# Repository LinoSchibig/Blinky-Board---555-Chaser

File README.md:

# Blinky Board - 555 Chaser

## Description
The Blinky Board is an LED chaser circuit developed for Stasis. It works with a NE555 timer and CD4017, creating a cicle of LEDs blinking.

I choose this project because it was recommeneded as beginner project

---

## Features
- 8 sequential LEDs forming a chasing light pattern  
- Adjustable speed using a potentiometer  
- Custom PCB designed in KiCad

---

## How It Works
The NE555 timer operates in astable mode and generates a continuous signal. This signal is fed into the CD4017, which gives one output per pulse.

Each output activates a LED, creating a "running light" effect. The speed of the pulse can be controlled by adjusting the potentiometer, which changes the timing of the NE555 timer.

---

## Why I Built This Project
Since quite some time ago, I have been interested in electronics and robotics. I saw an ad on Instagram and thought I should give it a try. I learned how to use Stasis and KiCad and started this recommended beginner project.

---

## Difficulties
- Understanding the correct wiring between the NE555 and CD4017 was confusing   
- Managing PCB layout constraints while keeping signal paths clean   

---

## What I Learned
- Basic PCB design principles in KiCad  
- Importance of correct grounding and stable power routing  

---

## Images

### Schematic

### PCB Design

### 3D-View

---

# BOM (Bill of Materials)

This is the list of components used for the project.

| Description | Reference | Qty | Value | Footprint | Source | Price |
|-------------|-----------|-----|-------|-----------|--------|-------|
| Unpolarized capacitor | C1 | 1 | 0.01 µF | Capacitor_THT:CP_Radial_D5.0mm_P2.00mm | DigiKey | $0.27 |
| Polarized capacitor | C2 | 1 | 1 µF | Capacitor_THT:C_Disc_D7.5mm_W2.5mm_P5.00mm | Distrelec | CHF 4.61 |
| Resistor | R2 | 1 | 470 Ω | Resistor_THT:R_Axial_DIN0207_L6.3mm_D2.5mm_P7.62mm_Horizontal | DigiKey | $0.10 |
| Resistor | R1 | 1 | 1 kΩ | Resistor_THT:R_Axial_DIN0207_L6.3mm_D2.5mm_P7.62mm_Horizontal | DigiKey | $0.10 |
| Johnson Counter (10 outputs) | U1 | 1 | CD4017BE | CD4017BE:DIP794W45P254L1969H508Q16 | DigiKey | $1.39 |
| Potentiometer | RV1 | 1 | 50 kΩ | Potentiometer_THT:Potentiometer_Vishay_T93YA_Vertical | DigiKey | $18.78 |
| Generic connector (1x01 socket) | J2 | 1 | Conn_01x01_Socket | Connector_PinHeader_2.54mm:PinHeader_1x01_P2.54mm_Vertical | DigiKey | $6.15 |
| Generic connector (1x02 socket) | J1 | 1 | Conn_01x02_Socket | Connector_PinHeader_2.54mm:PinHeader_1x02_P2.54mm_Vertical | DigiKey | $6.15 |
| Light emitting diode | D1, D2, D4, D5, D6, D7, D9, D10 | 8 | LED | LED_THT:LED_D3.0mm | Conrad | $3.95 |
| Precision Timer (555 compatible) | U2 | 1 | NE555P | Package_DIP:DIP-8_W7.62mm | Reichelt | $0.30 |

---

## Notes
All PCB fabrication files (Gerber ZIP) are included in the repository under `/pcb/production_files/`.

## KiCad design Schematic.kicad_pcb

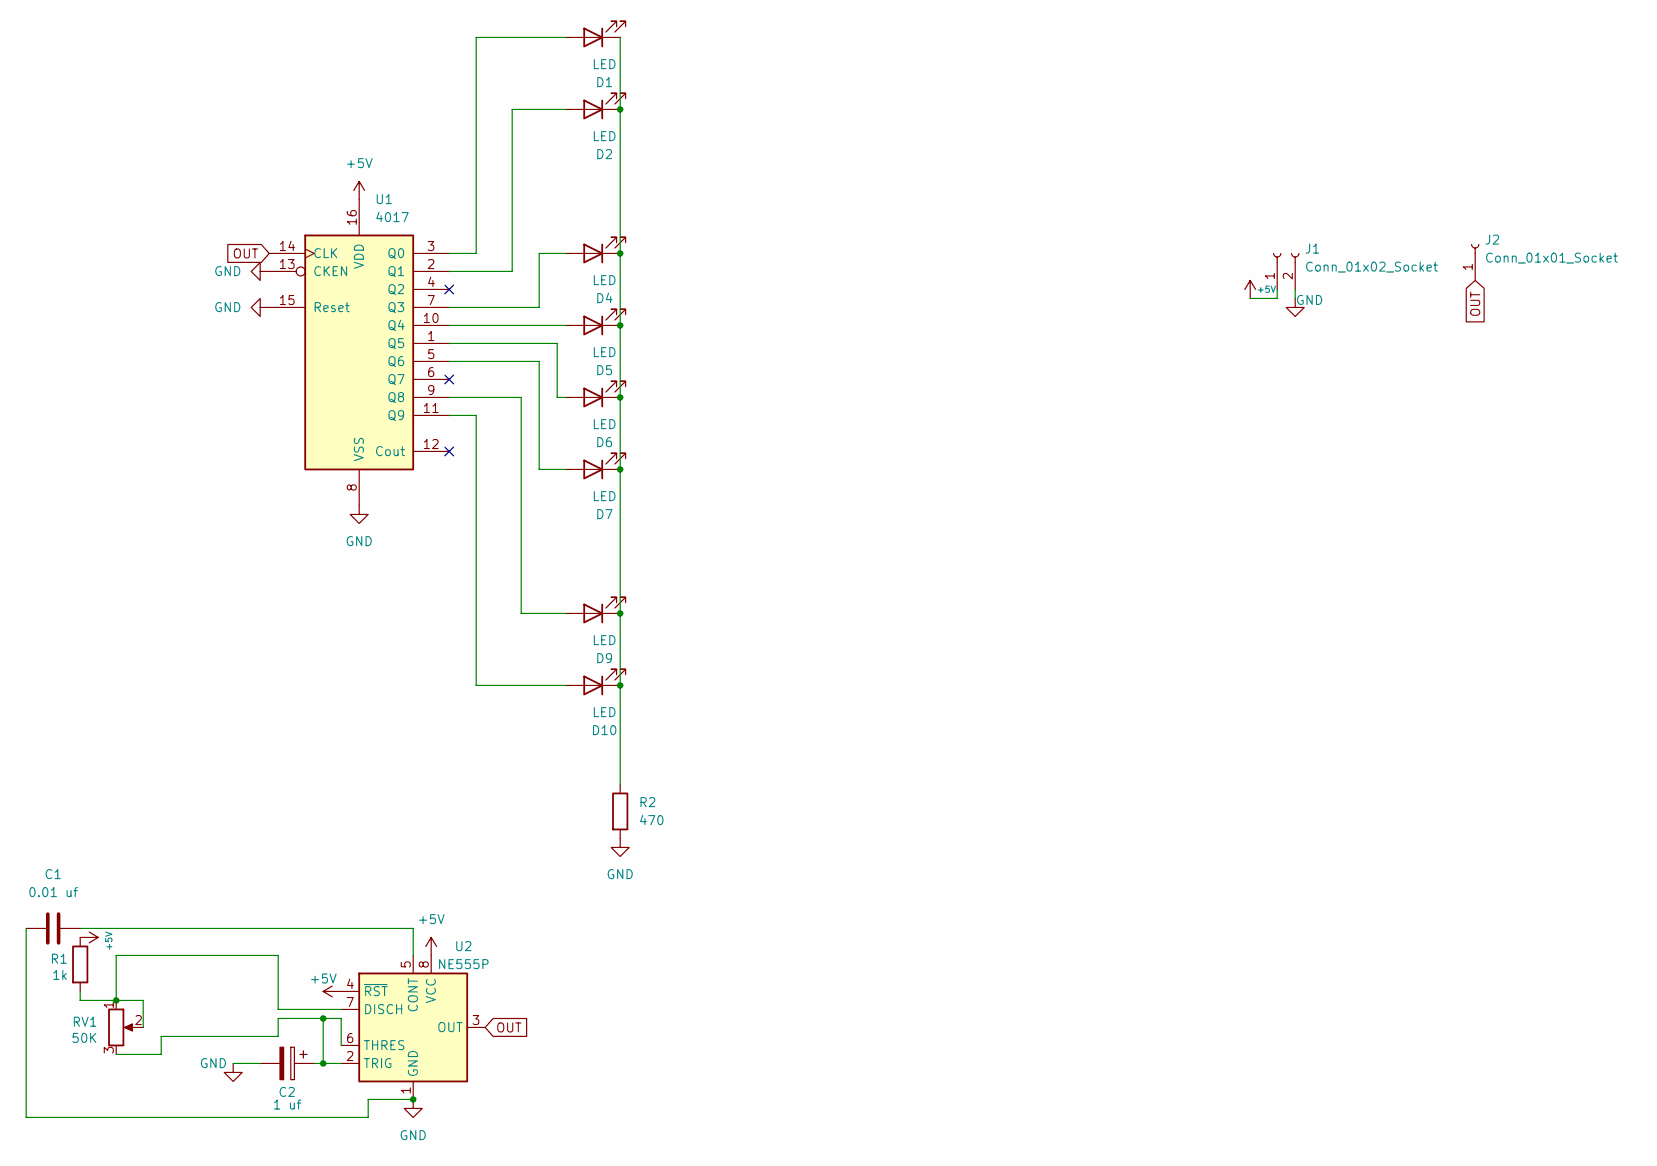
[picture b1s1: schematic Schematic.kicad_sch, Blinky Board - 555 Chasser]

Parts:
C1: 0.01 uf; CP_Radial_D5.0mm_P2.00mm
C2: 1 uf; C_Disc_D7.5mm_W2.5mm_P5.00mm
D1, D2, D4, D5, D6, D7, D9, D10: LED; LED_D3.0mm
J1: Conn_01x02_Socket; PinHeader_1x02_P2.54mm_Vertical
J2: Conn_01x01_Socket; PinHeader_1x01_P2.54mm_Vertical
R1: 1k; R_Axial_DIN0207_L6.3mm_D2.5mm_P7.62mm_Horizontal
R2: 470; R_Axial_DIN0207_L6.3mm_D2.5mm_P7.62mm_Horizontal
RV1: 50K; Potentiometer_Vishay_T93YA_Vertical
U1: 4017; DIP794W45P254L1969H508Q16
U2: NE555P; DIP-8_W7.62mm

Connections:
+5V: J1.1, R1.1, U1.16 (VDD), U2.4 (~RST), U2.8 (VCC)
GND: C1.1, C2.2, J1.2, R2.2, U1.8 (VSS), U1.13 (CKEN), U1.15 (Reset), U2.1 (GND)
unnamed: D1.2 (A), U1.3 (Q0)
unnamed: D1.1 (K), D2.1 (K), D4.1 (K), D5.1 (K), D6.1 (K), D7.1 (K), D9.1 (K), D10.1 (K), R2.1
unnamed: D2.2 (A), U1.2 (Q1)
unnamed: D4.2 (A), U1.7 (Q3)
unnamed: D5.2 (A), U1.10 (Q4)
unnamed: D6.2 (A), U1.1 (Q5)
unnamed: D7.2 (A), U1.5 (Q6)
unnamed: D9.2 (A), U1.9 (Q8)
unnamed: D10.2 (A), U1.11 (Q9)
unnamed: C1.2, U2.5 (CONT)
unnamed: R1.2, RV1.1, RV1.2, U2.7 (DISCH)
unnamed: C2.1, RV1.3, U2.2 (TRIG), U2.6 (THRES)
OUT: J2.1 (Pin_1_1), U1.14 (CLK), U2.3 (OUT)

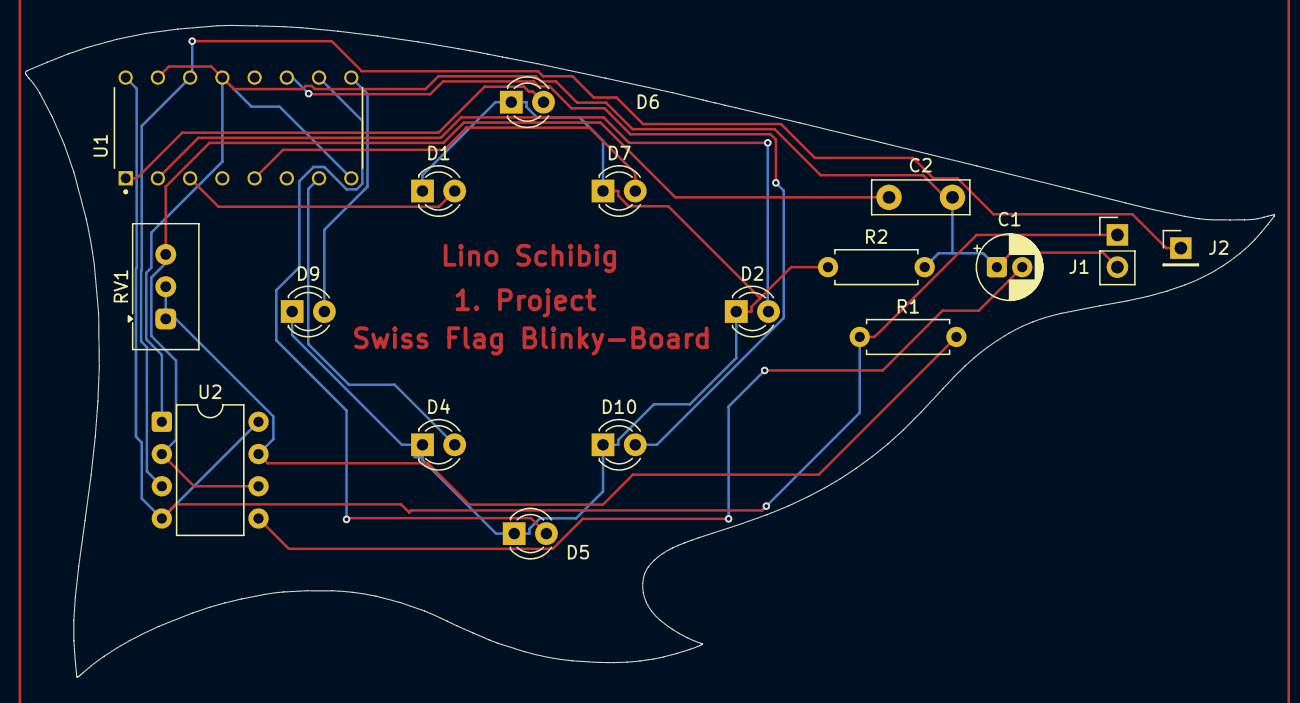
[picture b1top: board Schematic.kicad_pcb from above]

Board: 2 copper layers, 98.4 x 51.4 mm, 17 parts (0 on the bottom side), 15 nets.

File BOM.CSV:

Part;Qty;Price (USD);Link
CD4017BE;1;1.39;DigiKey CD4017BE
NE555P;1;0.65;Texas Instruments NE555P
LED (Red 5mm);8;0.10 each;DigiKey LEDs
Conn_01x02_Socket;1;0.15;DigiKey Connectors
Conn_01x01_Socket;1;0.1;DigiKey Connectors
Resistor 470 ?;1;0.02;DigiKey Resistors
Resistor 1 k?;1;0.02;DigiKey Resistors
Capacitor 0.01 µF;1;0.05;DigiKey Capacitors
Capacitor 1 µF;1;0.05;DigiKey Connectors
Potentiometer 50 k?;1;0.5;DigiKey Potentiometers
PCB Manufacturing;1;2;JLCPCB

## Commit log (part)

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2026-04-19 Fix heading formatting in README.md
2026-04-19 Fix project title formatting in README.md
2026-04-21 Add files via Upload
    I added the _pcb, _pro, _sch_ files + a screenshot from the 3D viewer.
2026-04-21 Add image to README for project visualization
    Added an image to the README for better visualization.
2026-05-12 Delete Schematic.kicad_pcb
    I deleted the file, because I have redesigned the PCB
2026-05-12 Delete Schematic.kicad_pro
    I deleted the file, because I have redesigned the PCB
2026-05-12 Delete Schematic.kicad_sch
    I deleted the file, because I have redesigned the PCB
2026-05-12 Delete Screenshot_3D_View.png
    I deleted the file, because I have redesigned the PCB
2026-05-12 Remove image from project description
    Removed image from README.md. I deleted the file, because I have redesigned the PCB.
2026-05-12 Add updated files
    I added the updated files from my project
2026-05-12 Add image to README for Blinky-Board project
    Added the updated image to the README for visual reference.
2026-06-18 Revise README for Blinky Board project
    Updated project description, features, and components list for clarity.
2026-06-25 Add BOM.csv file
    This is my Bill of Materials for the Project. I needed to add it for Stasis
2026-06-25 Add new files
    I Add all the updated and new Files
2026-06-25 Enhance README with project details and learnings
    Expanded project description and added sections on difficulties and learnings. Updated features and components list for clarity.
2026-06-28 Revise README for clarity and conciseness
    Updated project description, features, and learning outcomes for clarity and conciseness.
